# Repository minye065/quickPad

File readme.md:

# quickpad

A 3x3 macropad with 8 buttons and an encoder

Links to an app on my computer, change mode through the encoder and use the buttons to activate various shortcuts <br>
Shortcuts are streamed to the app which executes things (usually powershell commands) <br>
Still looking for ideas as there is an infinite number of things i can assign keys to (through changing mode through encoder) <br>

PLEASE NOTE THIS IS MADE FOR PERSONAL USE <br>
It has not been designed so that someone else would be able to use it, <br>

<br>
<br>

BOM
--
Printed out case
Seeed XIAO RP2040
EC11E Rotary encoder (with switch!)
4x M3x5mx4mm heatset inserts
4x M3x16mm screws
8x MX-Style switches
8x white blank DSA keycaps
--

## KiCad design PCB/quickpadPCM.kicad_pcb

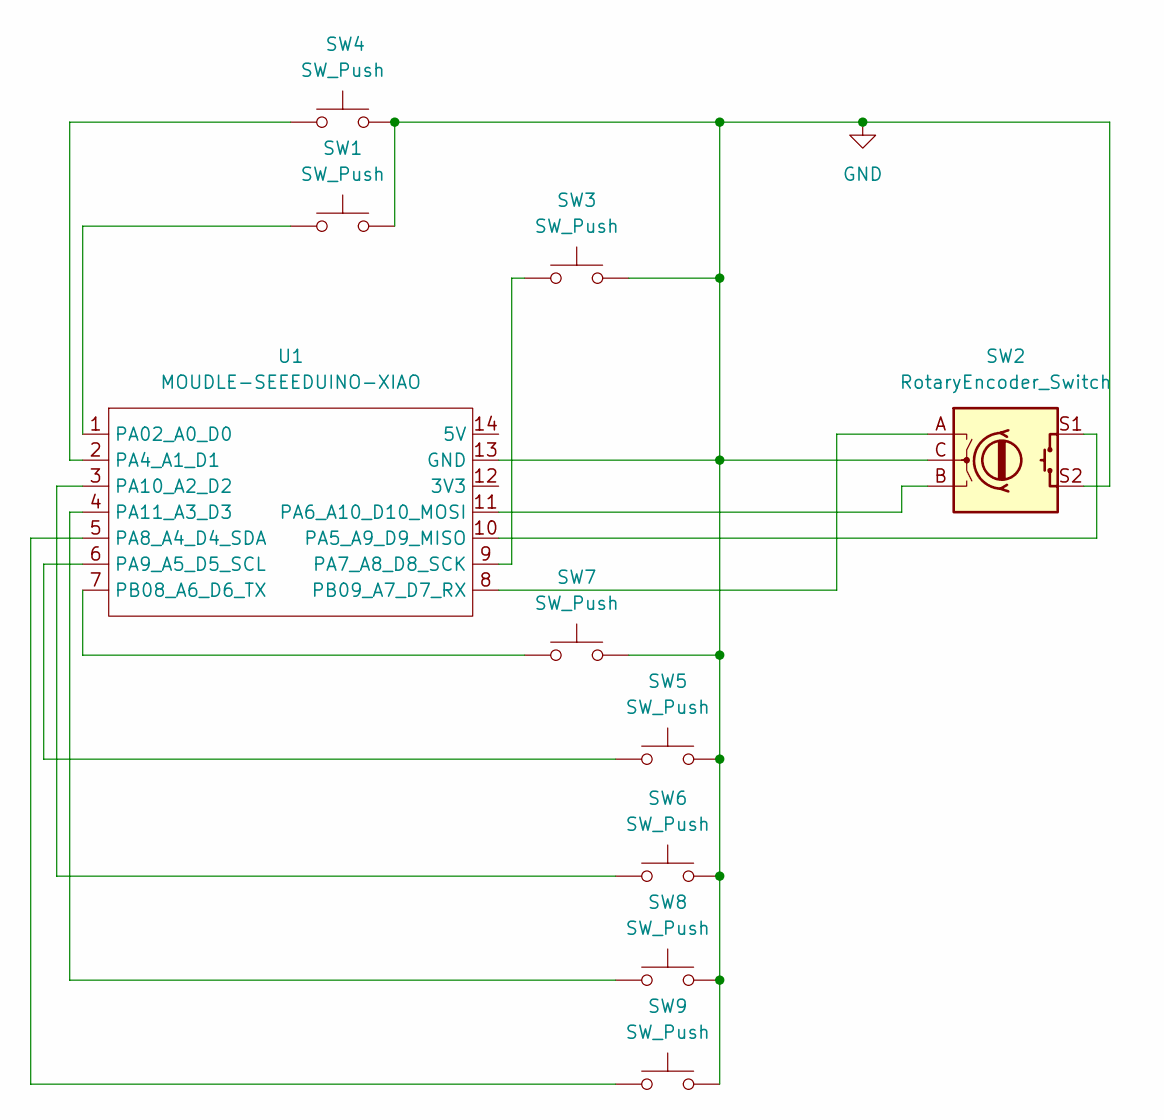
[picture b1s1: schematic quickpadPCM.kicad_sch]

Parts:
SW1, SW3, SW4, SW5, SW6, SW7, SW8, SW9: SW_Push; SW_Cherry_MX_1.00u_PCB
SW2: RotaryEncoder_Switch; RotaryEncoder_Alps_EC11E-Switch_Vertical_H20mm
U1: MOUDLE-SEEEDUINO-XIAO; XIAO-Generic-Hybrid-14P-2.54-21X17.8MM

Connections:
GND: SW1.2, SW2.C, SW2.S2, SW3.2, SW4.2, SW5.2, SW6.2, SW7.2, SW8.2, SW9.2, U1.13 (GND)
unnamed: SW1.1, U1.1 (PA02_A0_D0)
unnamed: SW4.1, U1.2 (PA4_A1_D1)
unnamed: SW2.S1, U1.10 (PA5_A9_D9_MISO)
unnamed: SW2.B, U1.11 (PA6_A10_D10_MOSI)
unnamed: SW3.1, U1.9 (PA7_A8_D8_SCK)
unnamed: SW9.1, U1.5 (PA8_A4_D4_SDA)
unnamed: SW5.1, U1.6 (PA9_A5_D5_SCL)
unnamed: SW6.1, U1.3 (PA10_A2_D2)
unnamed: SW8.1, U1.4 (PA11_A3_D3)
unnamed: SW7.1, U1.7 (PB08_A6_D6_TX)
unnamed: SW2.A, U1.8 (PB09_A7_D7_RX)

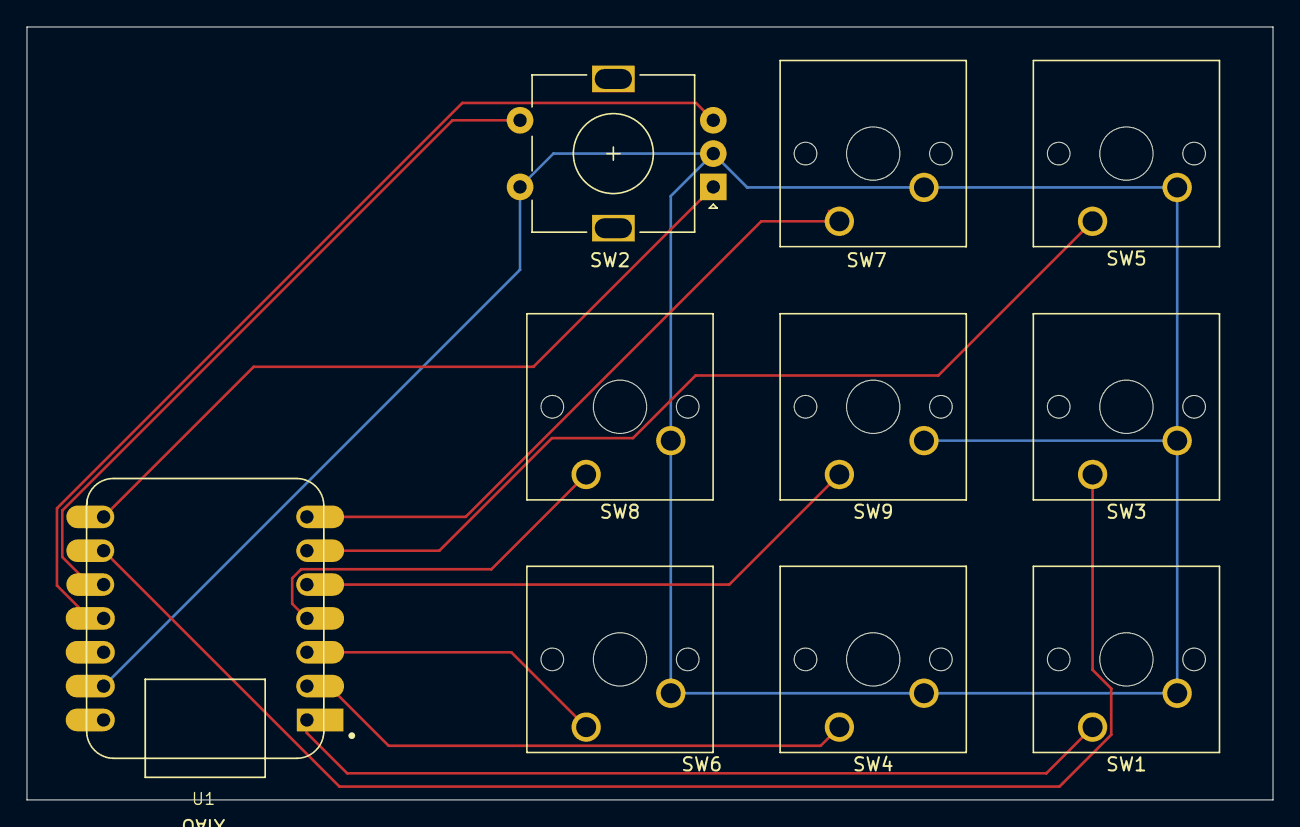
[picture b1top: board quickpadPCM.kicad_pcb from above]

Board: 2 copper layers, 93.5 x 58.0 mm, 10 parts (0 on the bottom side), 12 nets.
